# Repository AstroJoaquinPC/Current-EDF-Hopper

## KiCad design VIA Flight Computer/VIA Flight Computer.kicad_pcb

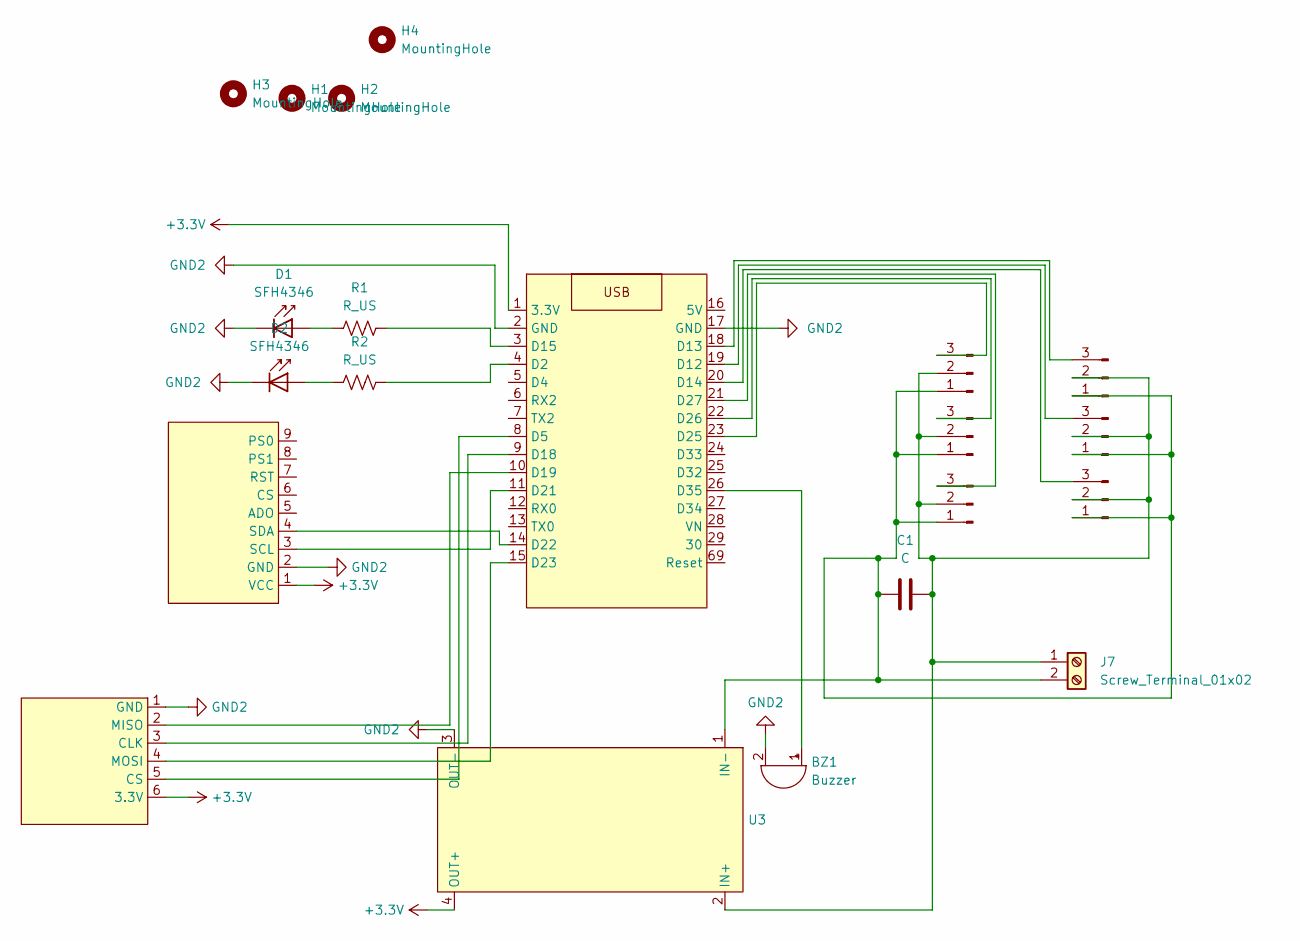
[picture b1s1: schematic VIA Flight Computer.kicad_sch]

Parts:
+X1: Conn_01x03_Pin; PinHeader_1x03_P2.54mm_Vertical
+Y1: Conn_01x03_Pin; PinHeader_1x03_P2.54mm_Vertical
-X1: Conn_01x03_Pin; PinHeader_1x03_P2.54mm_Vertical
-Y1: Conn_01x03_Pin; PinHeader_1x03_P2.54mm_Vertical
Alt1: Conn_01x03_Pin; PinHeader_1x03_P2.54mm_Vertical
BZ1: Buzzer; Buzzer_12x9.5RM7.6
C1: C; C_Radial_D10.0mm_H12.5mm_P5.00mm
D1, D2: SFH4346; LED_D3.0mm_IRBlack
H1, H2, H3, H4: MountingHole; MountingHole_4.3x6.2mm_M4_Pad
J7: Screw_Terminal_01x02; TerminalBlock_MetzConnect_Type059_RT06302HBWC_1x02_P3.50mm_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
R1, R2: R_US; R_Axial_DIN0204_L3.6mm_D1.6mm_P5.08mm_Horizontal
U1: ESP-32S
U2: BNO08X
U3: Buck Converter
U4: SD Card Reader
Z1: Conn_01x03_Pin; PinHeader_1x03_P2.54mm_Vertical

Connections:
+3.3V: U1.1 (3.3V), U2.1 (VCC), U3.4 (OUT+), U4.6 (3.3V)
GND2: BZ1.2 (-), D1.1 (K), D2.1 (K), U1.2 (GND), U1.17 (GND), U2.2 (GND), U3.3 (OUT-), U4.1 (GND)
unnamed: +X1.1, +Y1.1, -X1.1, -Y1.1, Alt1.1, C1.1, J7.2, U3.1 (IN-), Z1.1
unnamed: +X1.2, +Y1.2, -X1.2, -Y1.2, Alt1.2, C1.2, J7.1, U3.2 (IN+), Z1.2
unnamed: +X1.3, U1.20 (D14)
unnamed: +Y1.3, U1.22 (D26)
unnamed: -X1.3, U1.19 (D12)
unnamed: -Y1.3, U1.23 (D25)
unnamed: Alt1.3, U1.21 (D27)
unnamed: BZ1.1 (+), U1.26 (D35)
unnamed: D1.2 (A), R1.1
unnamed: D2.2 (A), R2.1
unnamed: R2.2, U1.4 (D2)
unnamed: U1.8 (D5), U4.5 (CS)
unnamed: U1.18 (D13), Z1.3
unnamed: R1.2, U1.3 (D15)
unnamed: U1.9 (D18), U4.3 (CLK)
unnamed: U1.10 (D19), U4.2 (MISO)
unnamed: U1.11 (D21), U2.3 (SCL)
unnamed: U1.14 (D22), U2.4 (SDA)
unnamed: U1.15 (D23), U4.4 (MOSI)

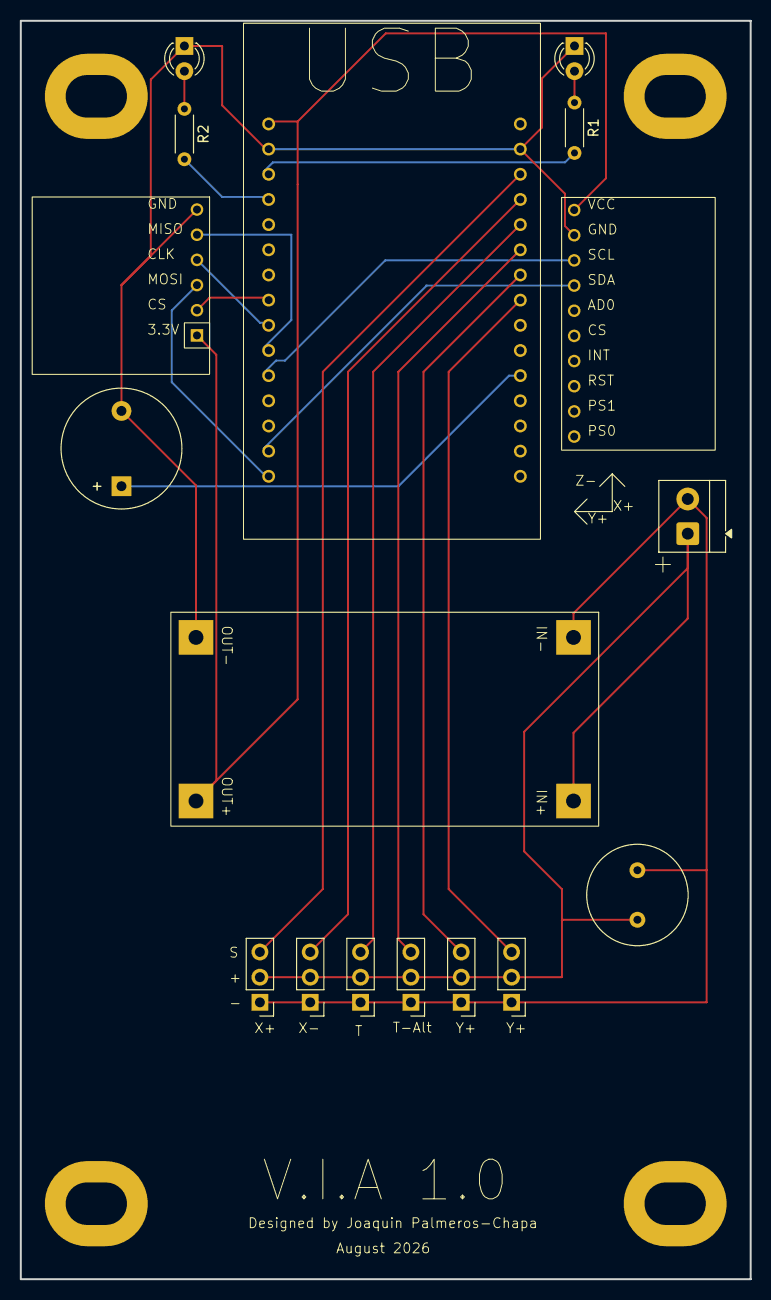
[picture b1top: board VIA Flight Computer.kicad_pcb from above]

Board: 2 copper layers, 73.7 x 127.0 mm, 21 parts (0 on the bottom side), 21 nets.
